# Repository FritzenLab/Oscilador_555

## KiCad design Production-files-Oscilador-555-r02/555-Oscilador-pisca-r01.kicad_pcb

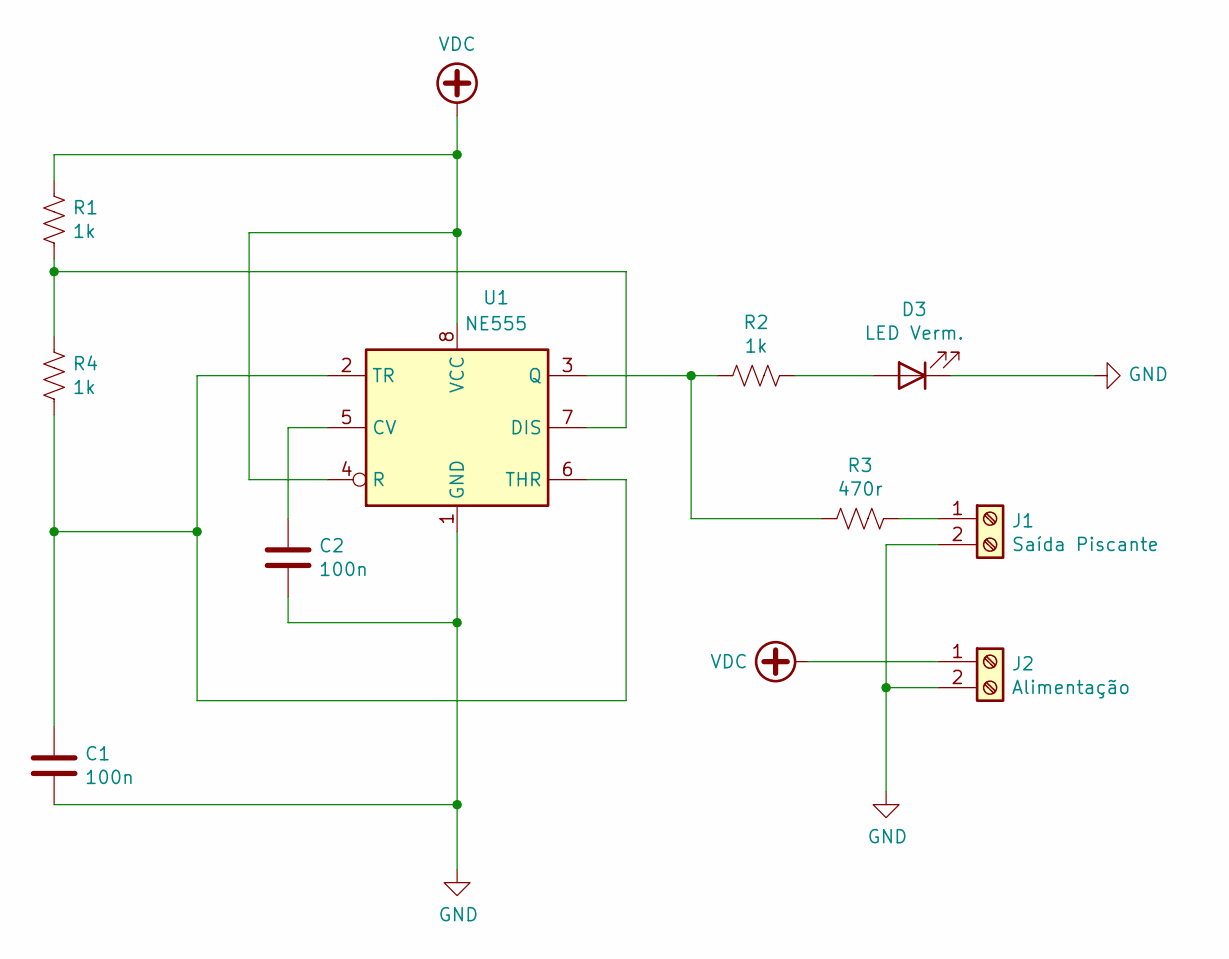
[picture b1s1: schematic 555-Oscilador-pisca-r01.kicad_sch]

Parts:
C1, C2: 100n; C_Disc_D3.0mm_W2.0mm_P2.50mm
D3: LED Verm.; LED_D5.0mm_Clear
J1: Saída Piscante; PhoenixContact_MCV_1,5_2-G-5.08_1x02_P5.08mm_Vertical
J2: Alimentação; PhoenixContact_MCV_1,5_2-G-5.08_1x02_P5.08mm_Vertical
R1, R2, R4: 1k; R_Axial_DIN0207_L6.3mm_D2.5mm_P10.16mm_Horizontal
R3: 470r; R_Axial_DIN0207_L6.3mm_D2.5mm_P10.16mm_Horizontal
U1: NE555; DIP-8_W7.62mm_Socket_LongPads

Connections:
GND: C1.2, C2.2, D3.1 (K), J1.2, J2.2, U1.1 (GND)
unnamed: D3.2 (A), R2.1
unnamed: J1.1, R3.1
unnamed: C2.1, U1.5 (CV)
unnamed: R1.2, R4.1, U1.7 (DIS)
unnamed: R2.2, R3.2, U1.3 (Q)
unnamed: C1.1, R4.2, U1.2 (TR), U1.6 (THR)
VDC: J2.1, R1.1, U1.4 (R), U1.8 (VCC)

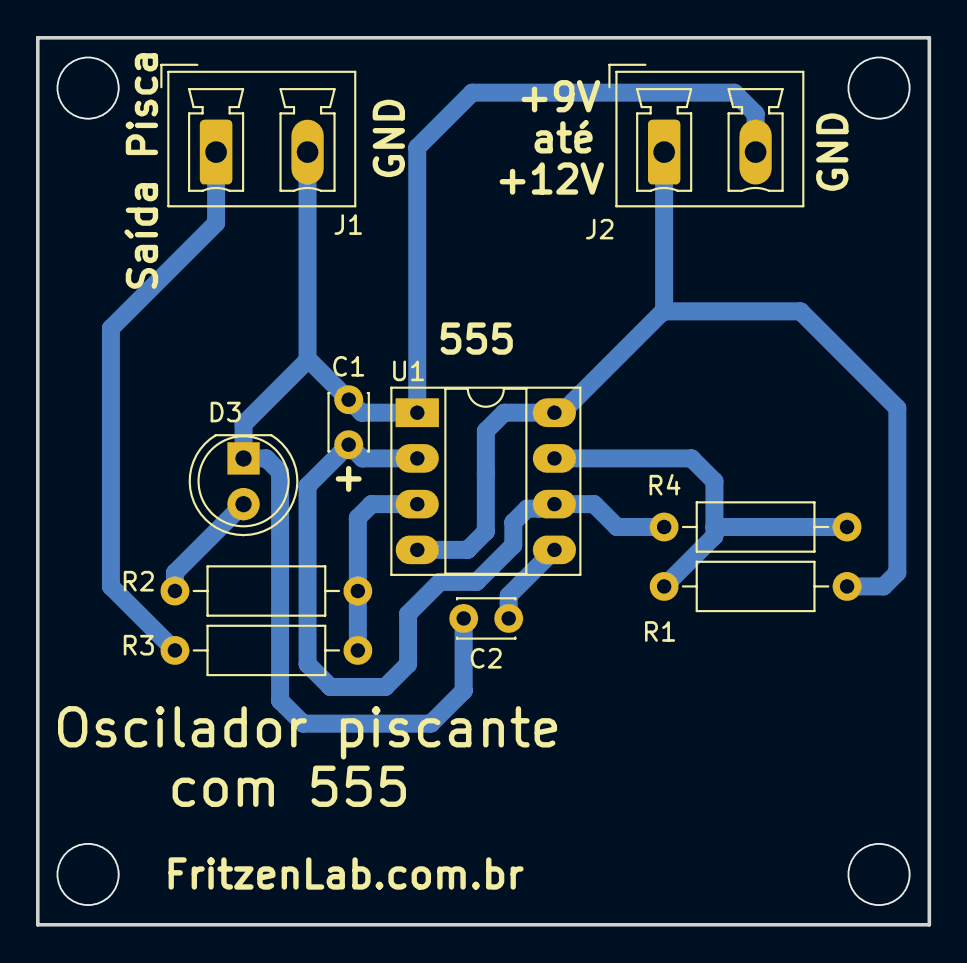
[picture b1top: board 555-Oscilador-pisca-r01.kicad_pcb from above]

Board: 2 copper layers, 49.5 x 49.3 mm, 10 parts (0 on the bottom side), 8 nets.

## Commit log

2016-03-02 Lançamento inicial de arquivos
    Arquivos em formato Eagle CADE (esquemático e layout de placa) do
    oscilador (pisca-pisca) educacional utilizando o CI 555
2016-04-01 Primeira revisao e arquivos zip para producao
    Primeira revisão (estética e para adicionar conector KRE 5mm); criado
    Gerber para producao da PCI
2019-02-10 revisado desenho da PCI
    revisado desenho da PCI
2019-02-10 arquivos de fabricacao
    arquivos de fabricacao
2024-11-02 backups
2024-11-03 generated gerbers
